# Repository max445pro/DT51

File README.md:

# DT51
The DT51 is a hombrew open source 8-bit computer based on the 8051 microcontroller architecture.

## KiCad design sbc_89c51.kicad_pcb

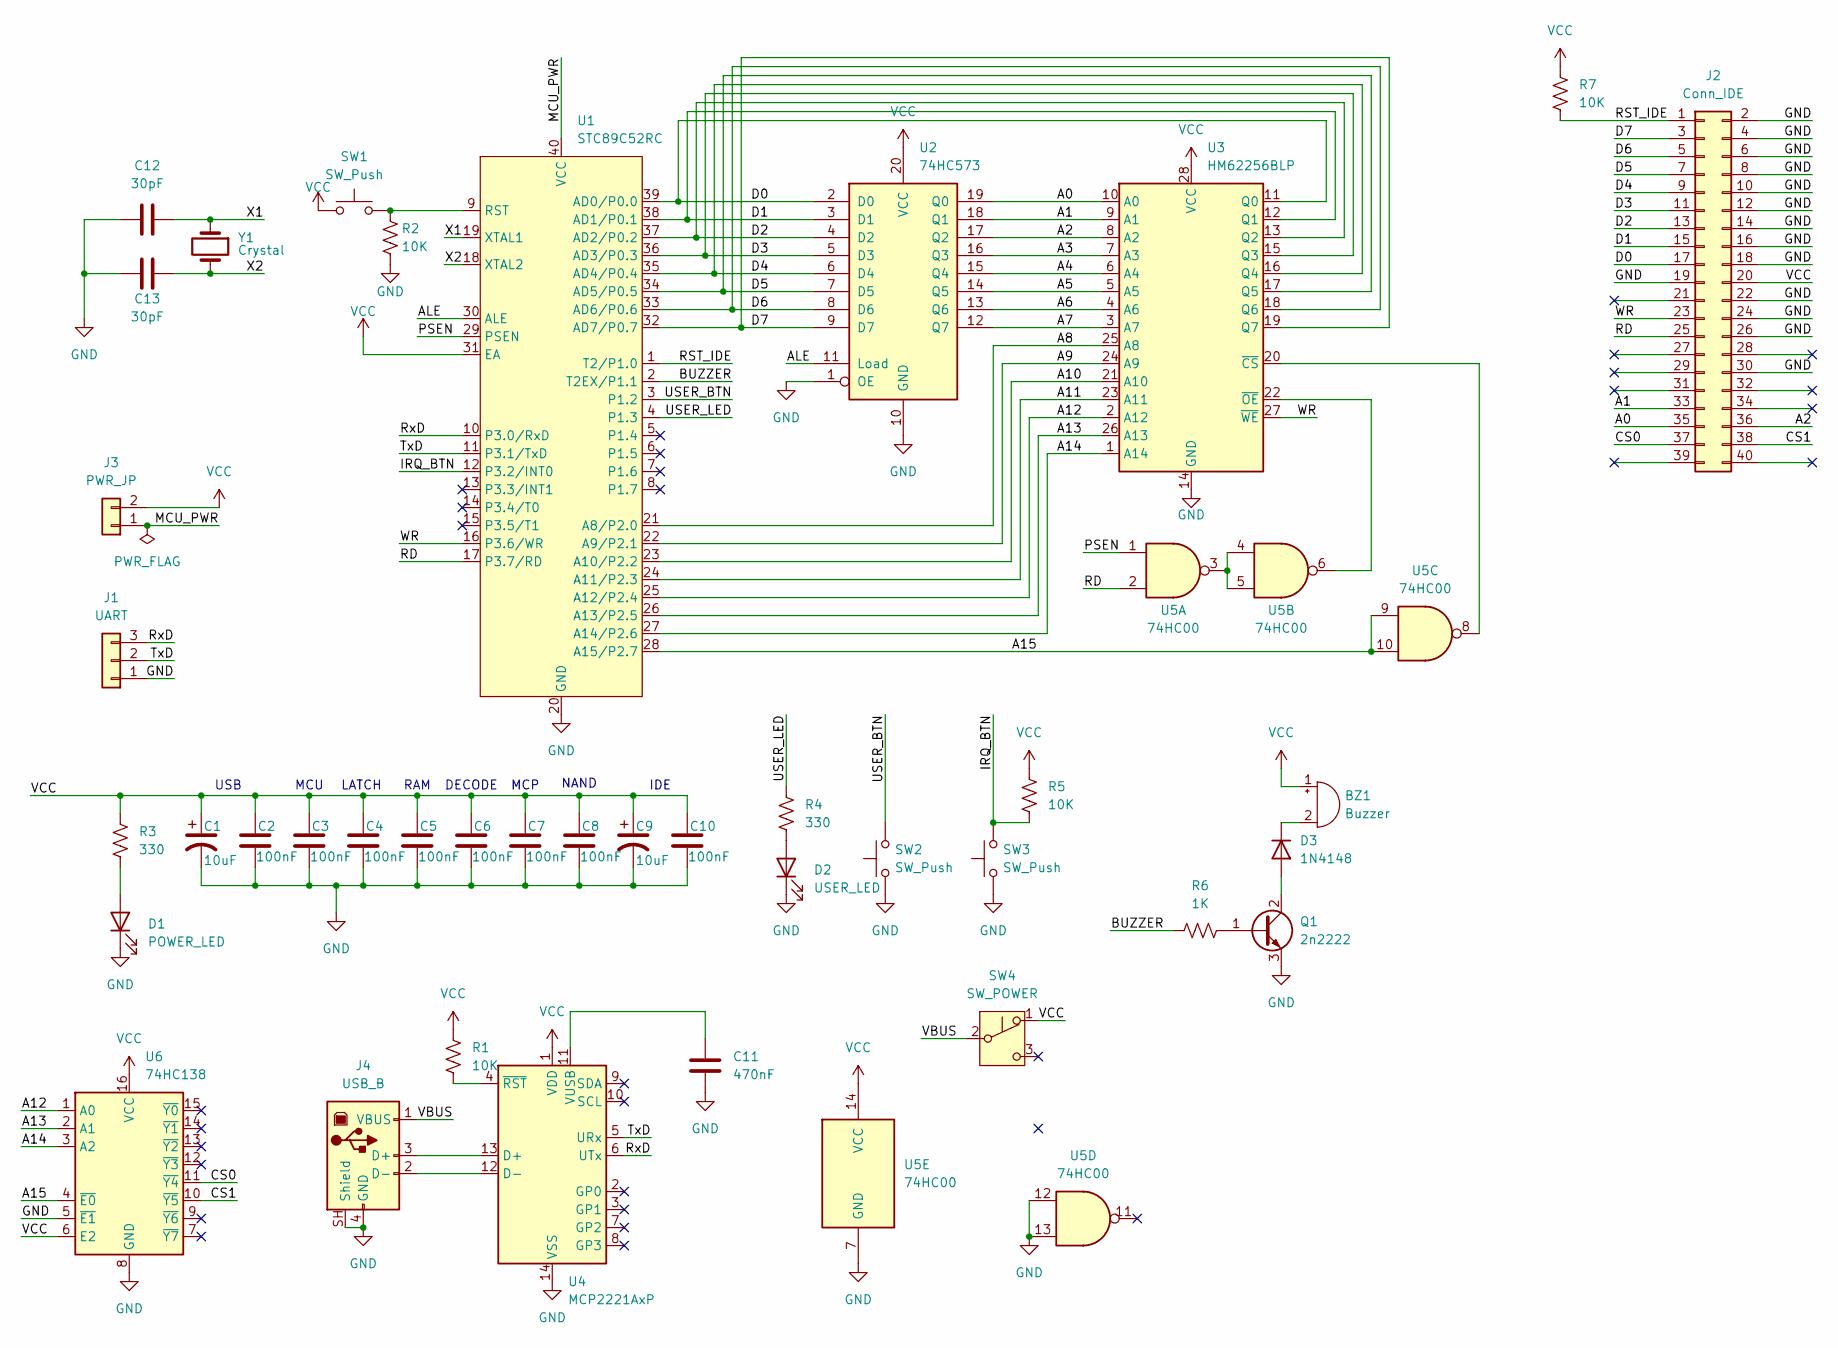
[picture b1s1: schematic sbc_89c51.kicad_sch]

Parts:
BZ1: Buzzer; Buzzer_12x9.5RM7.6
C1, C9: 10uF; CP_Radial_D5.0mm_P2.00mm
C2, C3, C4, C5, C6, C7, C8, C10: 100nF; C_Disc_D3.0mm_W2.0mm_P2.50mm
C11: 470nF; C_Disc_D3.0mm_W2.0mm_P2.50mm
C12, C13: 30pF; C_Disc_D3.0mm_W2.0mm_P2.50mm
D1: POWER_LED; LED_D5.0mm
D2: USER_LED; LED_D5.0mm
D3: 1N4148; D_DO-35_SOD27_P7.62mm_Horizontal
J1: UART; PinHeader_1x03_P2.54mm_Vertical
J2: Conn_IDE; IDC-Header_2x20_P2.54mm_Vertical
J3: PWR_JP; PinHeader_1x02_P2.54mm_Vertical
J4: USB_B; USB_B_Lumberg_2411_02_Horizontal
Q1: 2n2222; TO-92
R1, R2, R5, R7: 10K; R_Axial_DIN0207_L6.3mm_D2.5mm_P7.62mm_Horizontal
R3, R4: 330; R_Axial_DIN0207_L6.3mm_D2.5mm_P7.62mm_Horizontal
R6: 1K; R_Axial_DIN0207_L6.3mm_D2.5mm_P7.62mm_Horizontal
SW1, SW2, SW3: SW_Push; SW_TH_Tactile_Omron_B3F-100x
SW4: SW_POWER; PinHeader_1x03_P2.54mm_Vertical
U1: STC89C52RC; DIP-40_W15.24mm_Socket_LongPads
U2: 74HC573; DIP-20_W7.62mm_Socket_LongPads
U3: HM62256BLP; DIP-28_W15.24mm_Socket_LongPads
U4: MCP2221AxP; DIP-14_W7.62mm_Socket_LongPads
U5: 74HC00; DIP-14_W7.62mm_Socket_LongPads
U6: 74HC138; DIP-16_W7.62mm_Socket_LongPads
Y1: Crystal; Crystal_HC49-4H_Vertical

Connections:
/A0: J2.35, U2.19 (Q0), U3.10 (A0)
/A1: J2.33, U2.18 (Q1), U3.9 (A1)
/A2: J2.36, U2.17 (Q2), U3.8 (A2)
/A3: U2.16 (Q3), U3.7 (A3)
/A4: U2.15 (Q4), U3.6 (A4)
/A5: U2.14 (Q5), U3.5 (A5)
/A6: U2.13 (Q6), U3.4 (A6)
/A7: U2.12 (Q7), U3.3 (A7)
/A8: U1.21 (A8/P2.0), U3.25 (A8)
/A9: U1.22 (A9/P2.1), U3.24 (A9)
/A10: U1.23 (A10/P2.2), U3.21 (A10)
/A11: U1.24 (A11/P2.3), U3.23 (A11)
/A12: U1.25 (A12/P2.4), U3.2 (A12), U6.1 (A0)
/A13: U1.26 (A13/P2.5), U3.26 (A13), U6.2 (A1)
/A14: U1.27 (A14/P2.6), U3.1 (A14), U6.3 (A2)
/A15: U1.28 (A15/P2.7), U5.9, U5.10, U6.4 (~E0)
/ALE: U1.30 (ALE), U2.11 (Load)
/BUZZER: R6.1, U1.2 (T2EX/P1.1)
/CS0: J2.37, U6.11 (~Y4)
/CS1: J2.38, U6.10 (~Y5)
/D0: J2.17, U1.39 (AD0/P0.0), U2.2 (D0), U3.11 (Q0)
/D1: J2.15, U1.38 (AD1/P0.1), U2.3 (D1), U3.12 (Q1)
/D2: J2.13, U1.37 (AD2/P0.2), U2.4 (D2), U3.13 (Q2)
/D3: J2.11, U1.36 (AD3/P0.3), U2.5 (D3), U3.15 (Q3)
/D4: J2.9, U1.35 (AD4/P0.4), U2.6 (D4), U3.16 (Q4)
/D5: J2.7, U1.34 (AD5/P0.5), U2.7 (D5), U3.17 (Q5)
/D6: J2.5, U1.33 (AD6/P0.6), U2.8 (D6), U3.18 (Q6)
/D7: J2.3, U1.32 (AD7/P0.7), U2.9 (D7), U3.19 (Q7)
/IRQ_BTN: R5.2, SW3.2, U1.12 (P3.2/INT0)
/MCU_PWR: J3.1, U1.40 (VCC)
/PSEN: U1.29 (PSEN), U5.1
/RD: J2.25, U1.17 (P3.7/RD), U5.2
/RST_IDE: J2.1, R7.2, U1.1 (T2/P1.0)
/RxD: J1.3, U1.10 (P3.0/RxD), U4.6 (UTx)
/TxD: J1.2, U1.11 (P3.1/TxD), U4.5 (URx)
/USER_BTN: SW2.2, U1.3 (P1.2)
/USER_LED: R4.1, U1.4 (P1.3)
/VBUS: J4.1 (VBUS), SW4.2 (B)
/WR: J2.23, U1.16 (P3.6/WR), U3.27 (~WE)
/X1: C12.2, U1.19 (XTAL1), Y1.1
/X2: C13.2, U1.18 (XTAL2), Y1.2
GND: C1.2, C2.2, C3.2, C4.2, C5.2, C6.2, C7.2, C8.2, C9.2, C10.2, C11.2, C12.1, C13.1, D1.1 (K), D2.1 (K), J1.1, J2.2, J2.4, J2.6, J2.8, J2.10, J2.12, J2.14, J2.16, J2.18, J2.19, J2.22, J2.24, J2.26, J2.30, J4.4 (GND), J4.SH (Shield), Q1.3 (E), R2.1, SW2.1, SW3.1, U1.20 (GND), U2.1 (OE), U2.10 (GND), U3.14 (GND), U4.14 (VSS), U5.7 (GND), U5.12, U5.13, U6.5 (~E1), U6.8 (GND)
unnamed: BZ1.2 (-), D3.1 (K)
unnamed: D1.2 (A), R3.2
unnamed: D2.2 (A), R4.2
unnamed: D3.2 (A), Q1.2 (C)
unnamed: J4.3 (D+), U4.13 (D+)
unnamed: J4.2 (D-), U4.12 (D-)
unnamed: Q1.1 (B), R6.2
unnamed: R2.2, SW1.2, U1.9 (RST)
unnamed: U3.20 (~CS), U5.8
unnamed: U3.22 (~OE), U5.6
unnamed: C11.1, U4.11 (VUSB)
unnamed: R1.2, U4.4 (~RST)
unnamed: U5.3, U5.4, U5.5
VCC: BZ1.1 (+), C1.1, C2.1, C3.1, C4.1, C5.1, C6.1, C7.1, C8.1, C9.1, C10.1, J2.20, J3.2, R1.1, R3.1, R5.1, R7.1, SW1.1, SW4.1 (A), U1.31 (EA), U2.20 (VCC), U3.28 (VCC), U4.1 (VDD), U5.14 (VCC), U6.6 (E2), U6.16 (VCC)

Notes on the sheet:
LATCH
DECODE
MCP
NAND
IDE
USB
RAM
MCU

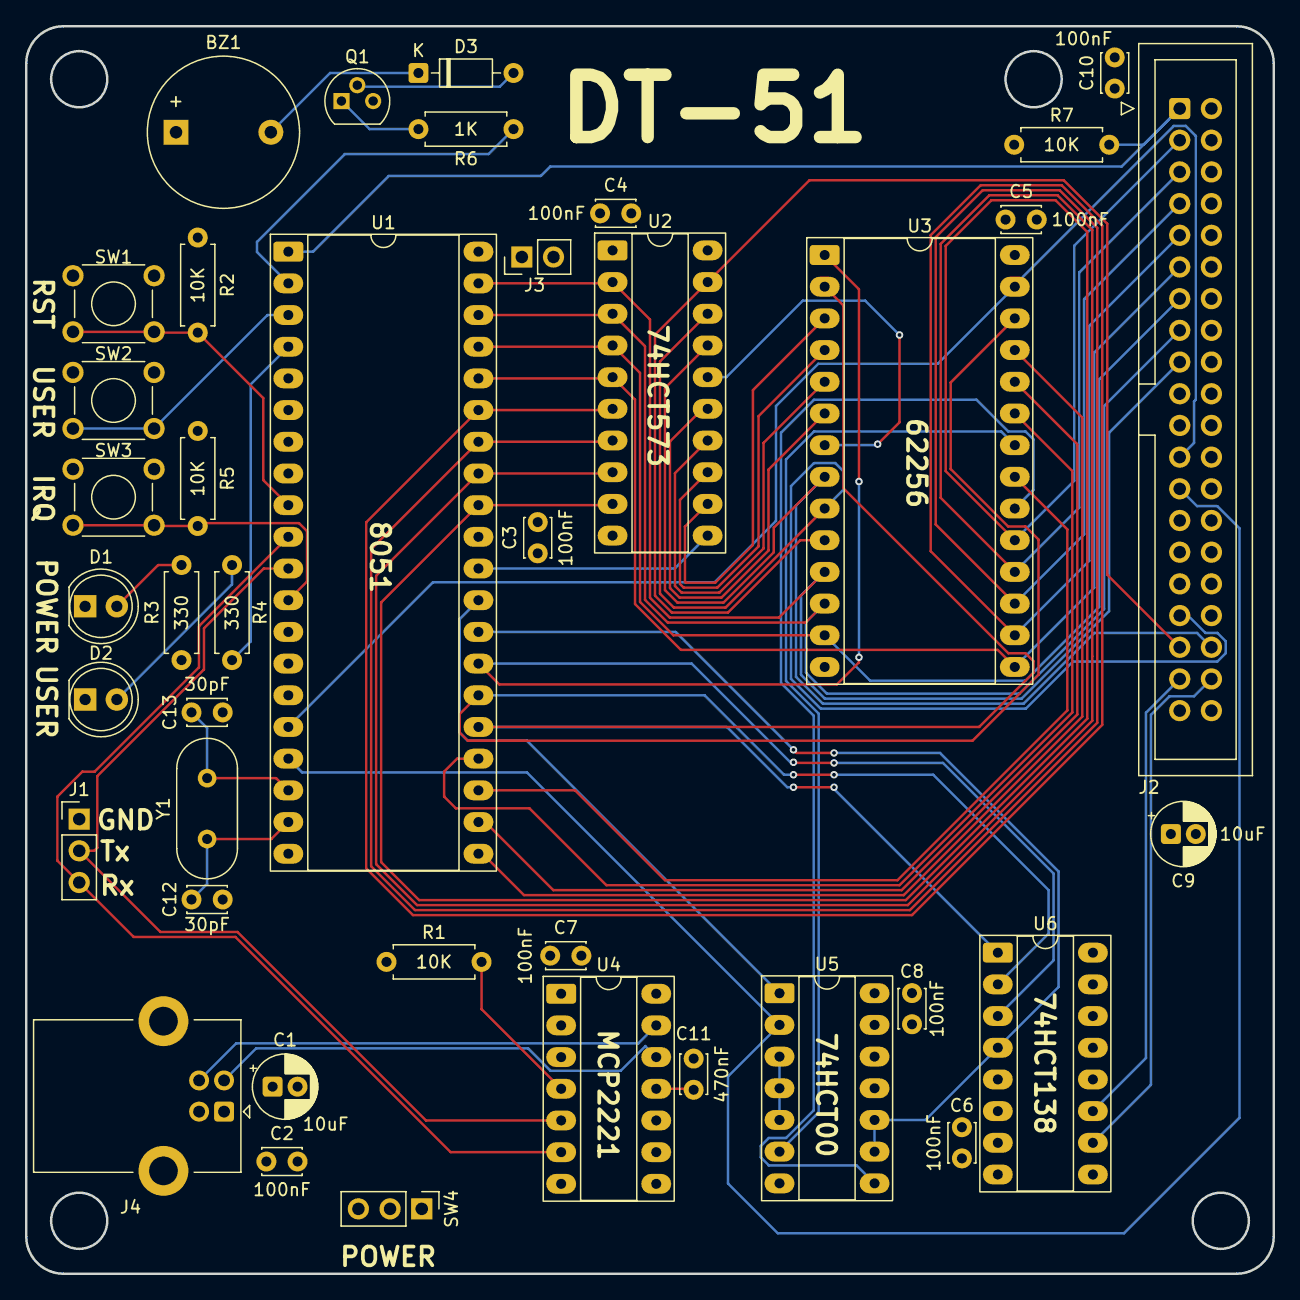
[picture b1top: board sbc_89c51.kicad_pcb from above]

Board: 4 copper layers, 100.0 x 100.0 mm, 40 parts (0 on the bottom side), 56 nets.
